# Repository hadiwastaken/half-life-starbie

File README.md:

# half-life-Starbie

* basically, this is a digital pet named Starbie and it is inspired by other digital pets also it contain diffrent sensors and components built on pcb bcause i want to learn PCB design and how things work in KICAD thatswhy i made this.

**FEATURES**
 * OLED display for displaying pet
 * A motion sensor named MPU6050 for tilt and shake interactions
 * Buttons to control pet and function
 * Built in pet
 * Customized PCB design
 * Microcontroller named XIAO ESP-32-C3

   **HOW IT WORKS**
   * SO THE ESP-32 ACTS AS THE BRAIN AND GATHERS DATA FROM DIFFRENT SENSORS AND FROM THE BUTTONS THEN THIS INFO IS PROCESSED TO CONTROL ANIMATION AND MENU NAVIGATION AND STATUS DISPLALYS ON THE OLED SCREEN.

   **IMAGES**

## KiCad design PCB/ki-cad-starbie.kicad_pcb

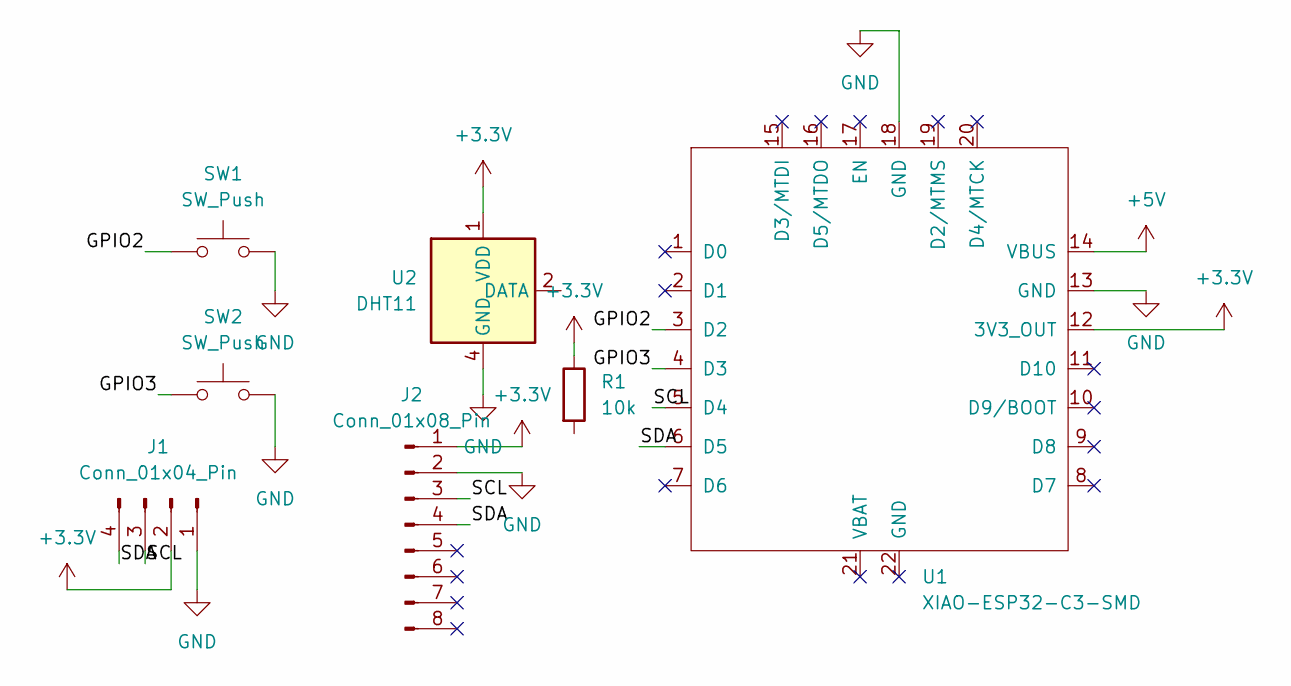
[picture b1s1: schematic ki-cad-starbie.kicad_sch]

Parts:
J1: Conn_01x04_Pin
J2: Conn_01x08_Pin
R1: 10k; Aosong_DHT11_5.5x12.0_P2.54mm
SW1: SW_Push; SW_NKK_GW12LJP
SW2: SW_Push
U1: XIAO-ESP32-C3-SMD
U2: DHT11; Aosong_DHT11_5.5x12.0_P2.54mm

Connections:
+3.3V: J1.2, J2.1, R1.1, U1.12 (3V3_OUT), U2.1 (VDD)
+5V: U1.14 (VBUS)
/DHT11 DATA: U1.2 (D1), U2.2 (DATA)
/GPIO2: SW1.1, U1.3 (D2)
/GPIO3: SW2.1, U1.4 (D3)
/SCL: J1.3, J2.3, U1.5 (D4)
/SDA: J1.4, J2.4, U1.6 (D5)
GND: J1.1, J2.2, SW1.2, SW2.2, U1.13 (GND), U1.18 (GND), U2.4 (GND)

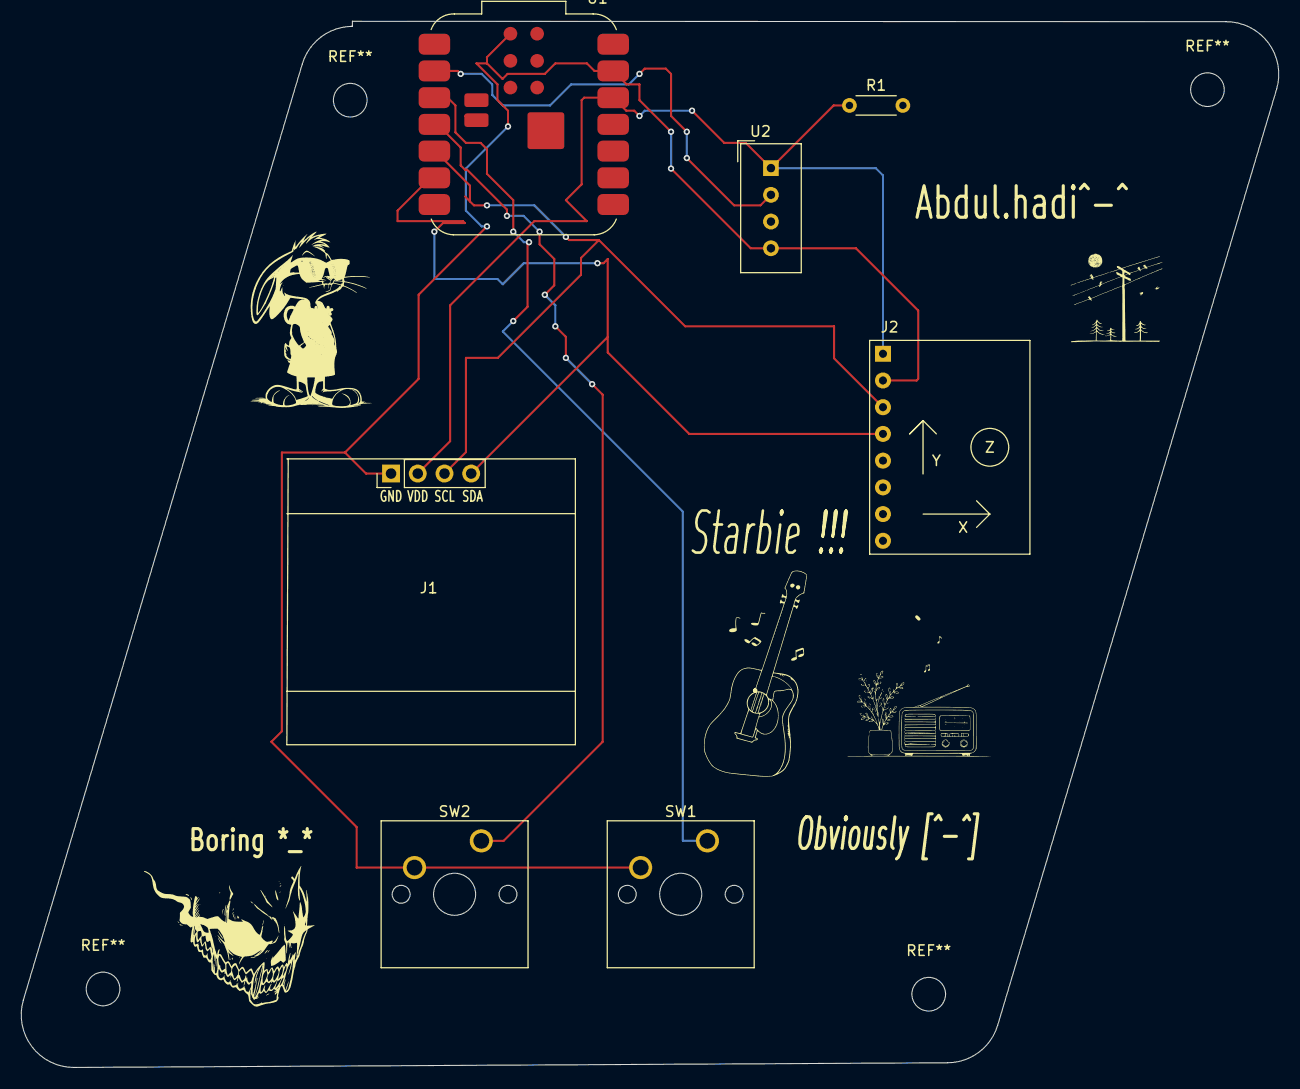
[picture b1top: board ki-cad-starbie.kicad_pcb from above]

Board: 2 copper layers, 119.5 x 99.5 mm, 10 parts (0 on the bottom side), 7 nets.

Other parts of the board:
., .#2: LOGO
`: LOGO
